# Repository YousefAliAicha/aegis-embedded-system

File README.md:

# AEGIS — Networked Rotating Ultrasonic Radar System

A real-time radar system built on the **Deneyap Kart 1A (ESP32-S3)**. AEGIS sweeps a servo-mounted HC-SR04 ultrasonic sensor across a 180° arc, streams live telemetry over WebSocket, and serves a full mission-control dashboard from the board itself — no external server, no app install, just a browser.

---

## Features

**Hardware**

- Continuous 0–180° servo sweep with configurable range, speed, and step size
- HC-SR04 ultrasonic ranging up to 300 cm
- 1602A LCD displaying live angle, distance, and detection state — flicker-free, no `clear()` in loop
- Graceful offline fallback: if Wi-Fi is unavailable the radar loop continues and the LCD remains live

**Web Dashboard** (served directly from the board at `http://<device-ip>`)

- Live radar scope with phosphor trail, sweep beam, and range rings
- Adjustable detection threshold ring rendered on-canvas
- **Manual Steer Mode** — click or drag on the radar canvas to aim the servo directly
- **Threat Perimeter** — draw a custom polygon on the radar; detections inside trigger a breach alarm
- Waterfall history strip showing distance over time
- Signal waveform panel with motion intensity meter
- Alert log with INNER / OUTER zone classification and unread badge counter
- **Audio Engine** — sonar ping tones scaled by target distance (Web Audio API)
- Animated globe widget with rotating world map and position marker
- System telemetry panel: CPU %, memory %, uptime, ESP32 chip temp
- Auto-reconnecting WebSocket — survives page reload and short network drops

**Firmware Controls** (all runtime-adjustable from the dashboard, no reflash needed)

| Command          | Effect                                |
| ---------------- | ------------------------------------- |
| `SET_SWEEP_MIN`  | Left boundary of sweep arc (0–180°)   |
| `SET_SWEEP_MAX`  | Right boundary of sweep arc (0–180°)  |
| `SET_STEP_DEG`   | Angular resolution per step (1–10°)   |
| `SET_STEP_DELAY` | Milliseconds between steps (5–200 ms) |
| `SET_THRESHOLD`  | Detection distance in cm (1–300 cm)   |
| `MANUAL_STEER`   | Point servo to a specific angle       |
| `AUTO_RESUME`    | Return to automatic sweep             |

▶ [Full demo on YouTube](https://youtu.be/lgbAfCLylXU)

---

## Hardware Requirements

| Component                      | Quantity | Notes                                                    |
| ------------------------------ | -------- | -------------------------------------------------------- |
| Deneyap Kart 1A                | 1        | ESP32-S3 based; other ESP32 boards require pin remapping |
| HC-SR04 Ultrasonic Sensor      | 1        | 5 V supply required                                      |
| SG90 Servo Motor               | 1        | 5 V supply required; never power from board 3.3 V        |
| 1602A LCD (HD44780-compatible) | 1        | 16-pin, 4-bit parallel mode                              |
| MB102 Breadboard Power Module  | 1        | Supplies 5 V to servo, sensor, and LCD                   |
| 9 V DC wall adapter            | 1        | Centre-positive, ≥ 1 A; **do not use a 9 V PP3 battery** |
| 10 kΩ potentiometer            | 1        | LCD contrast adjustment                                  |
| 220 Ω resistor                 | 1        | LCD backlight current limiting                           |

---

## Wiring

Full pin-level connection map is in **[WIRING.md](WIRING.md)**.

Quick summary:

| Deneyap Pin | Connected to                             |
| ----------- | ---------------------------------------- |
| D0          | SG90 PWM signal                          |
| D1          | HC-SR04 TRIG                             |
| D11         | HC-SR04 ECHO                             |
| D4          | LCD Enable                               |
| D5–D7       | LCD D4–D6                                |
| D10         | LCD RS                                   |
| D12         | LCD D7                                   |
| GND         | MB102 GND rail (mandatory common ground) |

> **Critical:** The MB102 GND rail **must** be wired to the Deneyap Kart GND pin. Without a shared ground reference all signal levels are undefined.

---

## Software Setup

### 1. Prerequisites

- [Arduino IDE 2.x](https://www.arduino.cc/en/software) (or Arduino CLI)
- Deneyap Kart board package installed in Arduino IDE
  - Add this URL under _File → Preferences → Additional boards manager URLs_:
    ```
    https://raw.githubusercontent.com/deneyapkart/deneyapkart-arduino-core/master/package_deneyapkart_index.json
    ```
  - Then install **Deneyap Kart** via _Tools → Board → Boards Manager_

### 2. Install Required Libraries

Open _Tools → Manage Libraries_ and install:

| Library     | Author           |
| ----------- | ---------------- |
| WebSockets  | Markus Sattler   |
| ESP32Servo  | Kevin Harrington |
| ArduinoJson | Benoit Blanchon  |

`LiquidCrystal` and `WiFi` are bundled with the Deneyap / ESP32 board package and require no separate install.

### 3. Configure Wi-Fi Credentials

Copy the example secrets file and fill in your network details:

```bash
cp firmware/aegis-deneyap/secrets.h.example firmware/aegis-deneyap/secrets.h
```

Edit `secrets.h`:

```cpp
#define WIFI_SSID     "your_network_name"
#define WIFI_PASSWORD "your_password"
```

> **`secrets.h` is listed in `.gitignore` and will never be committed.**

### 4. Flash the Board

1. Open `firmware/aegis-deneyap/aegis-deneyap.ino` in Arduino IDE
2. Select _Tools → Board → Deneyap Kart 1A_
3. Select the correct COM port under _Tools → Port_
4. Click **Upload**

On first boot the LCD will display `AEGIS v1.0` then `Connecting WiFi`. Once connected, the LCD shows the board's IP address for ~3 seconds before the radar loop begins.

### 5. Open the Dashboard

On any device connected to the same Wi-Fi network, open a browser and navigate to:

```
http://<ip shown on lcd or in serial monitor 115200>
```

The dashboard loads instantly — it is served directly from the board's flash memory. No internet connection is required after the fonts load on first visit (or if you remove the Google Fonts import from `dashboard.h` for fully offline use).

---

## Project Structure

```
aegis-embedded-system/
├── assets/                   # Images and media
├── firmware/
│   └── aegis-deneyap/
│       ├── aegis-deneyap.ino # Main firmware — radar loop, Wi-Fi, WebSocket server
│       ├── dashboard.h       # Self-contained HTML/CSS/JS dashboard, stored in ESP32 flash
│       ├── secrets.h         # Wi-Fi credentials — NOT committed (see .gitignore)
│       └── secrets.h.example # Template — copy this to secrets.h
├── hardware/
│   ├── aegis.kicad_sch       # KiCad schematic
│   ├── aegis.kicad_pcb       # KiCad PCB layout
│   ├── aegis.kicad_pro       # KiCad project file
│   └── HC-SR04/              # HC-SR04 sensor symbol/footprint reference
├── .gitignore
├── README.md
└── WIRING.md                 # Full pin-level wiring reference
```

---

## How It Works

AEGIS runs a **non-blocking sweep loop** — there is no `delay()` in the main loop. Each tick is gated by a millisecond timer, which keeps the WebSocket and HTTP stacks responsive between steps.

**Data flow:**

```
[Servo position] → [HC-SR04 pulse] → [distance measurement]
       ↓                                        ↓
  [LCD update]                     [WebSocket broadcast]
                                            ↓
                                   [Browser radar canvas]
```

**Inbound commands** from the browser arrive as JSON over WebSocket port 81 and are applied immediately to the live sweep parameters — no reflash, no restart.

**Offline mode:** if Wi-Fi association fails after 30 attempts (~12 seconds), AEGIS displays `OFFLINE MODE` on the LCD and continues the radar loop locally. The dashboard is unavailable in this state but all hardware functions normally.

---

## WebSocket Protocol

The board broadcasts one frame per sweep step on **port 81**.

**Outbound (board → browser):**

```json
{ "a": 90, "d": 34.2, "det": true }
```

- `a` — current servo angle (0–180°)
- `d` — measured distance in cm, or `-1` if out of range
- `det` — `true` if distance is within the detection threshold

**Inbound (browser → board):** see the [Firmware Controls](#firmware-controls) table above.

---

## License

MIT License — see [LICENSE](LICENSE) for full terms.
base) PS C:\Users\Yousef\Desktop\aegis-embedded-system> git add .
warning: in the working copy of 'firmware/aegis-deneyap/secrets.h', LF will be replaced by CRLF the next time Git touches it
warning: adding embedded git repository: hardware/.history
hint: You've added another git repository inside your current repository.
hint: Clones of the outer repository will not contain the contents of
hint: the embedded repository and will not know how to obtain it.
hint: If you meant to add a submodule, use:
hint:
hint: git submodule add <url> hardware/.history
hint:
hint: If you added this path by mistake, you can remove it from the
hint: index with:
hint:
hint: git rm --cached hardware/.history
hint:
hint: See "git help submodule" for more information.
hint: Disable this message with "git config set advice.addEmbeddedRepo false"
(base) PS C:\Users\Yousef\Desktop\aegis-embedded-system>

---

## Acknowledgements

- [WebSockets library](https://github.com/Links2004/arduinoWebSockets) — Markus Sattler
- [ESP32Servo](https://github.com/madhephaestus/ESP32Servo) — Kevin Harrington
- [ArduinoJson](https://arduinojson.org) — Benoit Blanchon
- Deneyap Kart hardware and board support — [Deneyap](https://deneyapkart.org)
- [HC-SR04 KiCad Model](https://www.snapeda.com/parts/HC-SR04/SparkFun/view-part/) — SparkFun

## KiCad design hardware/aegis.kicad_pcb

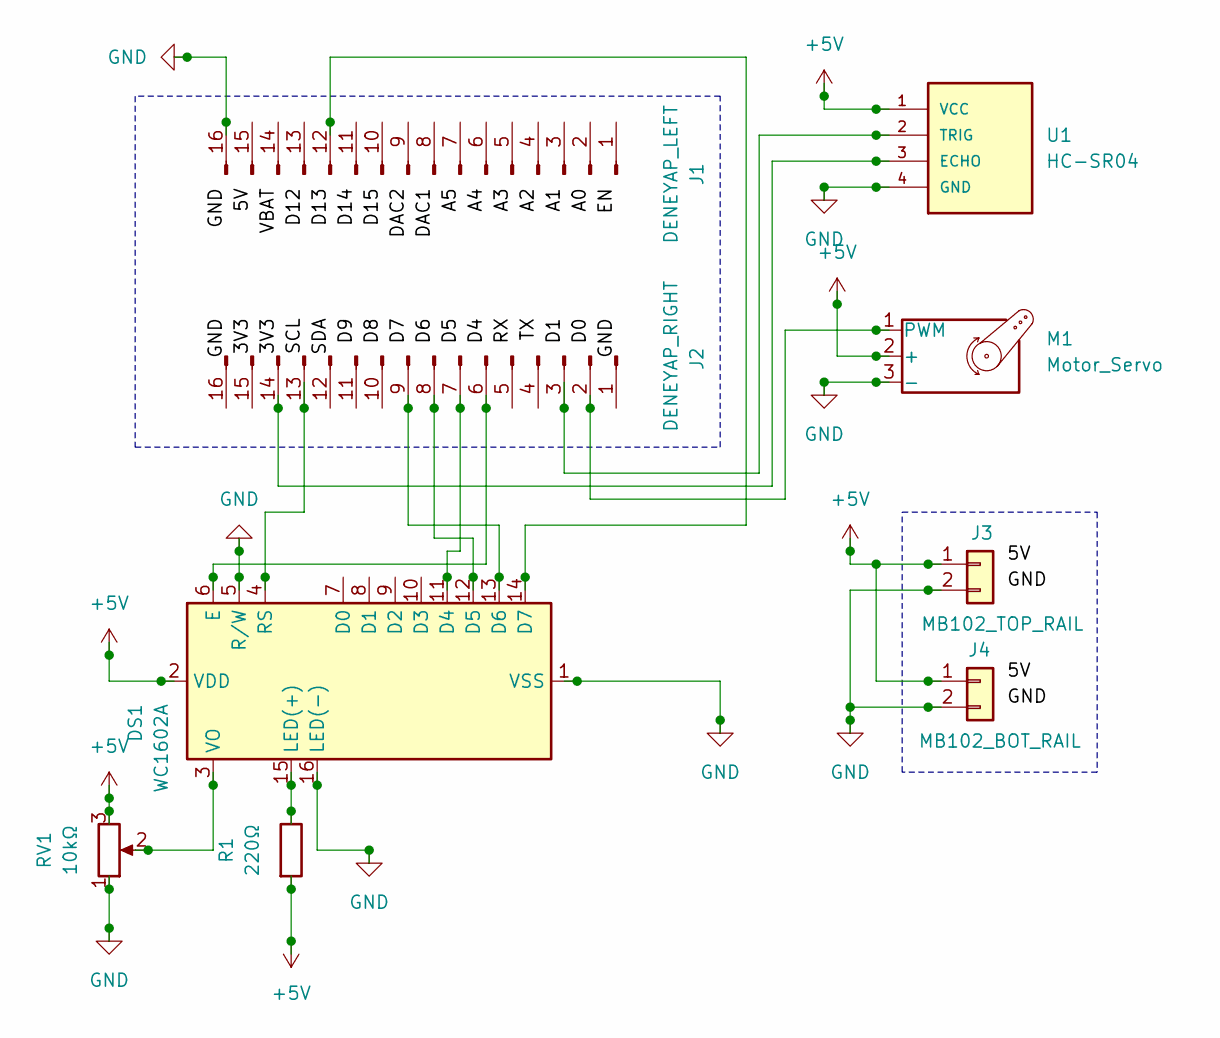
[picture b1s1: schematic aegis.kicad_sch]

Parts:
DS1: WC1602A
J1: DENEYAP_LEFT; PinHeader_1x16_P2.54mm_Vertical
J2: DENEYAP_RIGHT; PinHeader_1x16_P2.54mm_Vertical
J3: MB102_TOP_RAIL; PinHeader_1x02_P2.54mm_Vertical
J4: MB102_BOT_RAIL; PinHeader_1x02_P2.54mm_Vertical
M1: Motor_Servo; Harwin_M20-89003xx_1x03_P2.54mm_Horizontal
R1: 220Ω; R_0201_0603Metric
RV1: 10kΩ; Potentiometer_Bourns_3296W_Vertical
U1: HC-SR04; XCVR_HC-SR04

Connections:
+5V: DS1.2 (VDD), J3.1, J4.1, M1.2 (+), R1.2, RV1.3, U1.1 (VCC)
GND: DS1.1 (VSS), DS1.5 (R/W), DS1.16 (LED(-)), J1.16, J3.2, J4.2, M1.3 (-), RV1.1, U1.4 (GND)
unnamed: DS1.11 (D4), J2.7
unnamed: DS1.12 (D5), J2.8
unnamed: DS1.13 (D6), J2.9
unnamed: DS1.14 (D7), J1.12
unnamed: DS1.6 (E), J2.6
unnamed: DS1.15 (LED(+)), R1.1
unnamed: DS1.4 (RS), J2.13
unnamed: DS1.3 (VO), RV1.2
unnamed: J2.2, M1.1 (PWM)
unnamed: J2.3, U1.2 (TRIG)
unnamed: J2.14, U1.3 (ECHO)

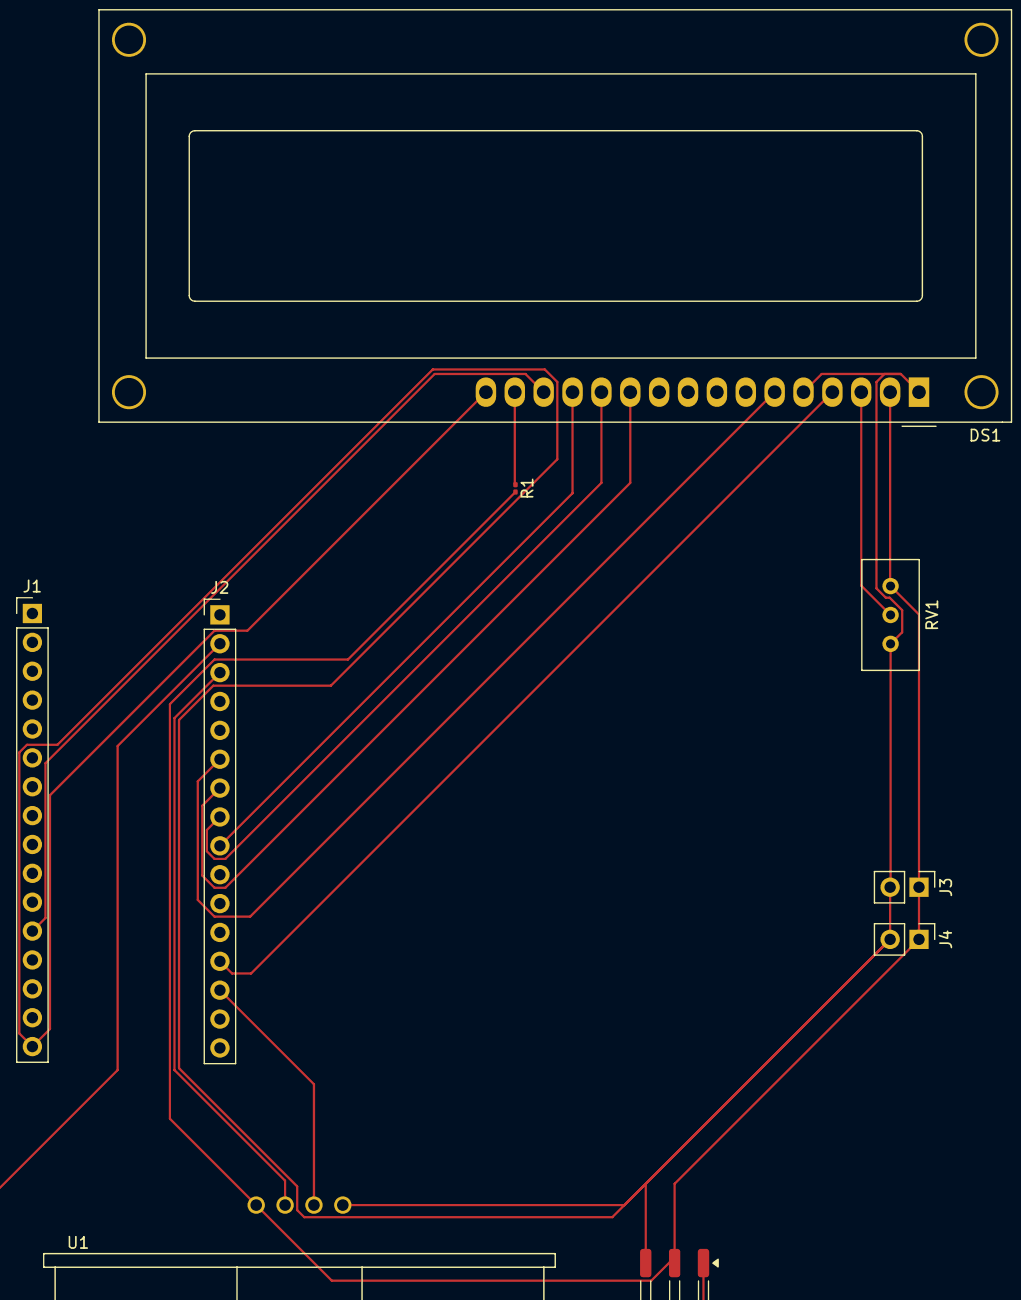
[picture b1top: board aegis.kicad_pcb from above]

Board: 2 copper layers, 9 parts (0 on the bottom side), 13 nets.

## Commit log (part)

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2026-06-28 Initial commit with firmware, hardware files, and assets
